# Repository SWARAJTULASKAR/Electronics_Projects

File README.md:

# Electronics_Projects
This repository showcases a collection of custom PCB design projects created using KiCad, Autodesk Fusion 360, and Autodesk EAGLE. Each project includes complete design files, simulations, 3D models, and fabrication-ready outputs.

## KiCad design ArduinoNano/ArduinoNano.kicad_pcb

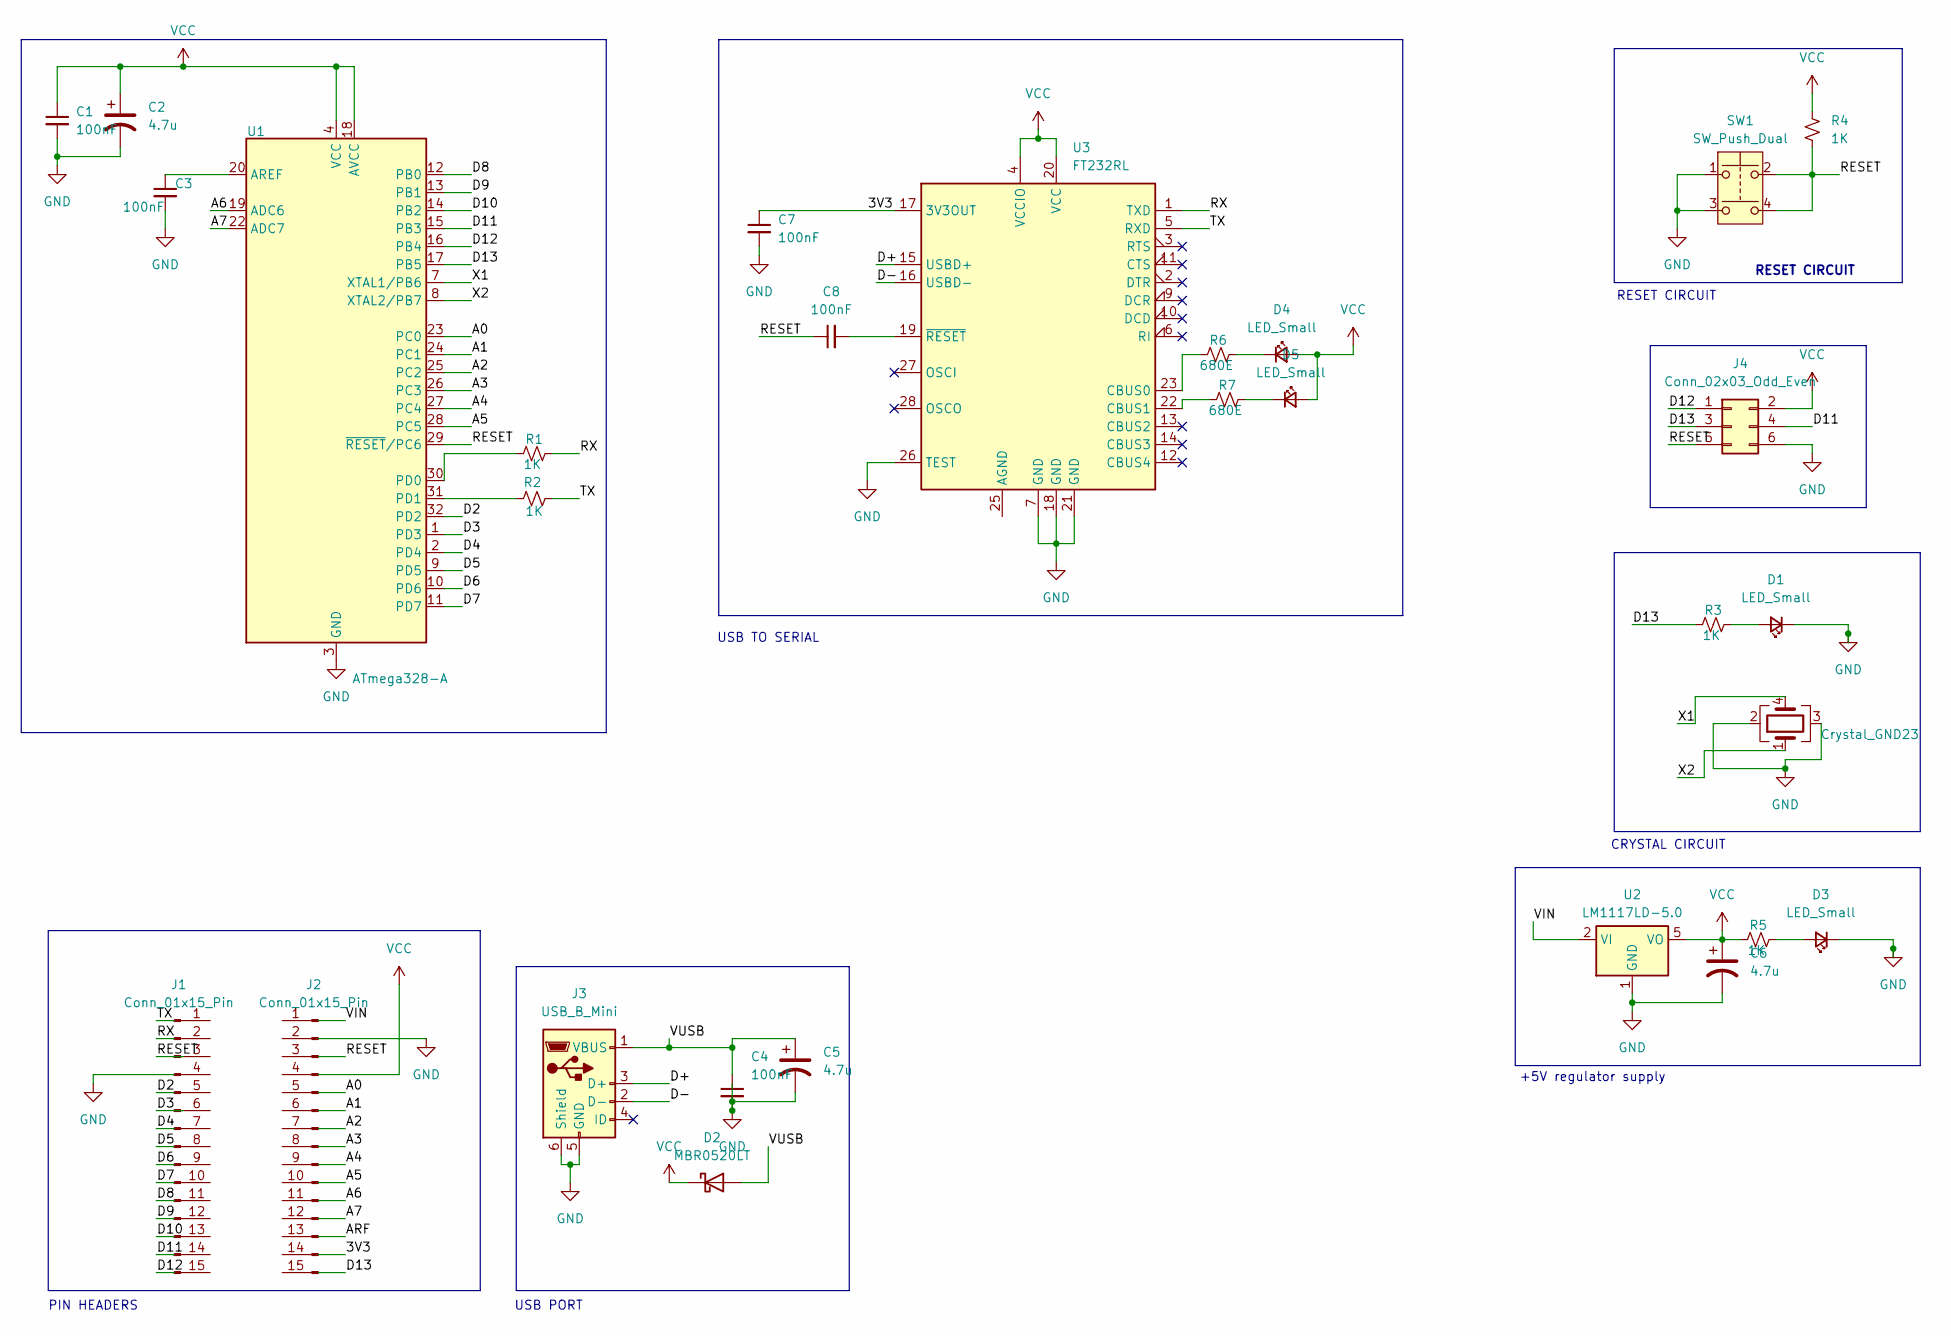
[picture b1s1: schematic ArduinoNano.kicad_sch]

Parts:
C1, C3, C4, C7, C8: 100nF; C_0603_1608Metric
C2, C5, C6: 4.7u; CP_EIA-1608-08_AVX-J
D1, D3, D4, D5: LED_Small; LED_1206_3216Metric
D2: MBR0520LT; D_SOD-123
J1, J2: Conn_01x15_Pin; Samtec_HPM-15-01-x-S_Straight_1x15_Pitch5.08mm
J3: USB_B_Mini; USB_Mini-B_Lumberg_2486_01_Horizontal
J4: Conn_02x03_Odd_Even; PinHeader_2x03_P2.54mm_Vertical
R1, R2, R3, R4, R5: 1K; R_01005_0402Metric
R6, R7: 680E; R_0402_1005Metric
SW1: SW_Push_Dual; SW_MEC_5GSH9
U1: ATmega328-A; TQFP-32_7x7mm_P0.8mm
U2: LM1117LD-5.0; WSON-8-1EP_4x4mm_P0.8mm_EP2.2x3mm
U3: FT232RL; SSOP-28_5.3x10.2mm_P0.65mm
Y1: Crystal_GND23; Crystal_SMD_Abracon_ABM3B-4Pin_5.0x3.2mm

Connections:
/3V3: C7.1, U3.17 (3V3OUT)
/A0: U1.23 (PC0)
/A1: U1.24 (PC1)
/A2: U1.25 (PC2)
/A3: U1.26 (PC3)
/A4: U1.27 (PC4)
/A5: U1.28 (PC5)
/A6: U1.19 (ADC6)
/A7: U1.22 (ADC7)
/D2: U1.32 (PD2)
/D3: U1.1 (PD3)
/D4: U1.2 (PD4)
/D5: U1.9 (PD5)
/D6: U1.10 (PD6)
/D7: U1.11 (PD7)
/D8: U1.12 (PB0)
/D9: U1.13 (PB1)
/D10: U1.14 (PB2)
/D11: J4.4, U1.15 (PB3)
/D12: J4.1, U1.16 (PB4)
/D13: J4.3, R3.1, U1.17 (PB5)
/D+: J3.3 (D+), U3.15 (USBD+)
/D-: J3.2 (D-), U3.16 (USBD-)
/RESET: C8.1, J4.5, R4.2, SW1.2, SW1.4, U1.29 (~RESET/PC6)
/RX: R1.2, U3.1 (TXD)
/TX: R2.2, U3.5 (RXD)
/VIN: U2.2 (VI), U2.3 (VI), U2.4 (VI)
/VUSB: C4.1, C5.1, D2.2 (A), J3.1 (VBUS)
GND: C1.2, C2.2, C3.2, C4.2, C5.2, C6.2, C7.2, D1.1 (K), D3.1 (K), J3.5 (GND), J3.6 (Shield), J4.6, SW1.1, SW1.3, U1.3 (GND), U1.5 (GND), U1.21 (GND), U2.1 (GND), U3.7 (GND), U3.18 (GND), U3.21 (GND), U3.26 (TEST), Y1.2, Y1.3
unnamed: D1.2 (A), R3.2
unnamed: D3.2 (A), R5.2
unnamed: D4.1 (K), R6.2
unnamed: D5.1 (K), R7.2
unnamed: C3.1, U1.20 (AREF)
unnamed: R1.1, U1.30 (PD0)
unnamed: R2.1, U1.31 (PD1)
unnamed: R6.1, U3.23 (CBUS0)
unnamed: R7.1, U3.22 (CBUS1)
unnamed: C8.2, U3.19 (~RESET)
VCC: C1.1, C2.1, C6.1, D2.1 (K), D4.2 (A), D5.2 (A), J4.2, R4.1, R5.1, U1.4 (VCC), U1.6 (VCC), U1.18 (AVCC), U2.5 (VO), U2.6 (VO), U2.7 (VO), U2.9 (VO), U3.4 (VCCIO), U3.20 (VCC)

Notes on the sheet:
CRYSTAL CIRCUIT
USB TO SERIAL
+5V regulator supply
PIN HEADERS
RESET CIRCUIT
RESET CIRCUIT
USB PORT

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
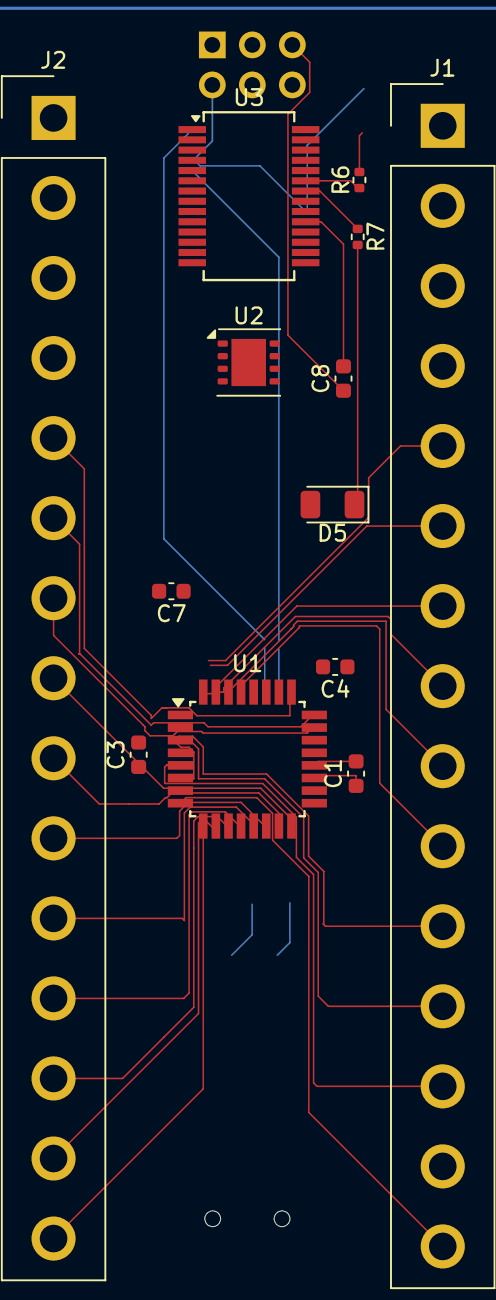
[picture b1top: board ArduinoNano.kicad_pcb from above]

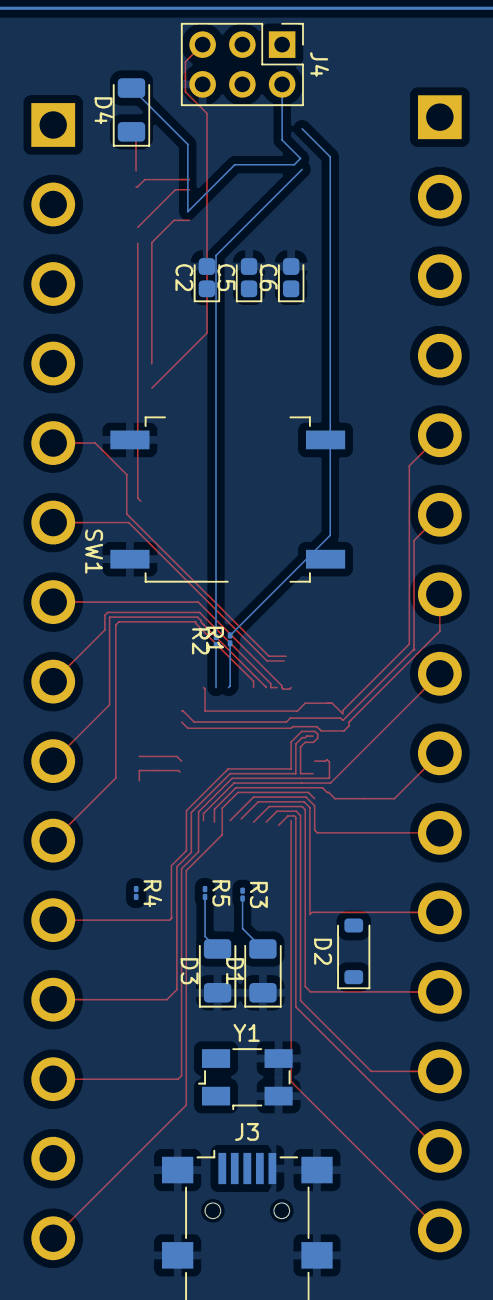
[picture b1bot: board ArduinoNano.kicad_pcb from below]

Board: 2 copper layers, 29 parts (16 on the bottom side), 25 nets.

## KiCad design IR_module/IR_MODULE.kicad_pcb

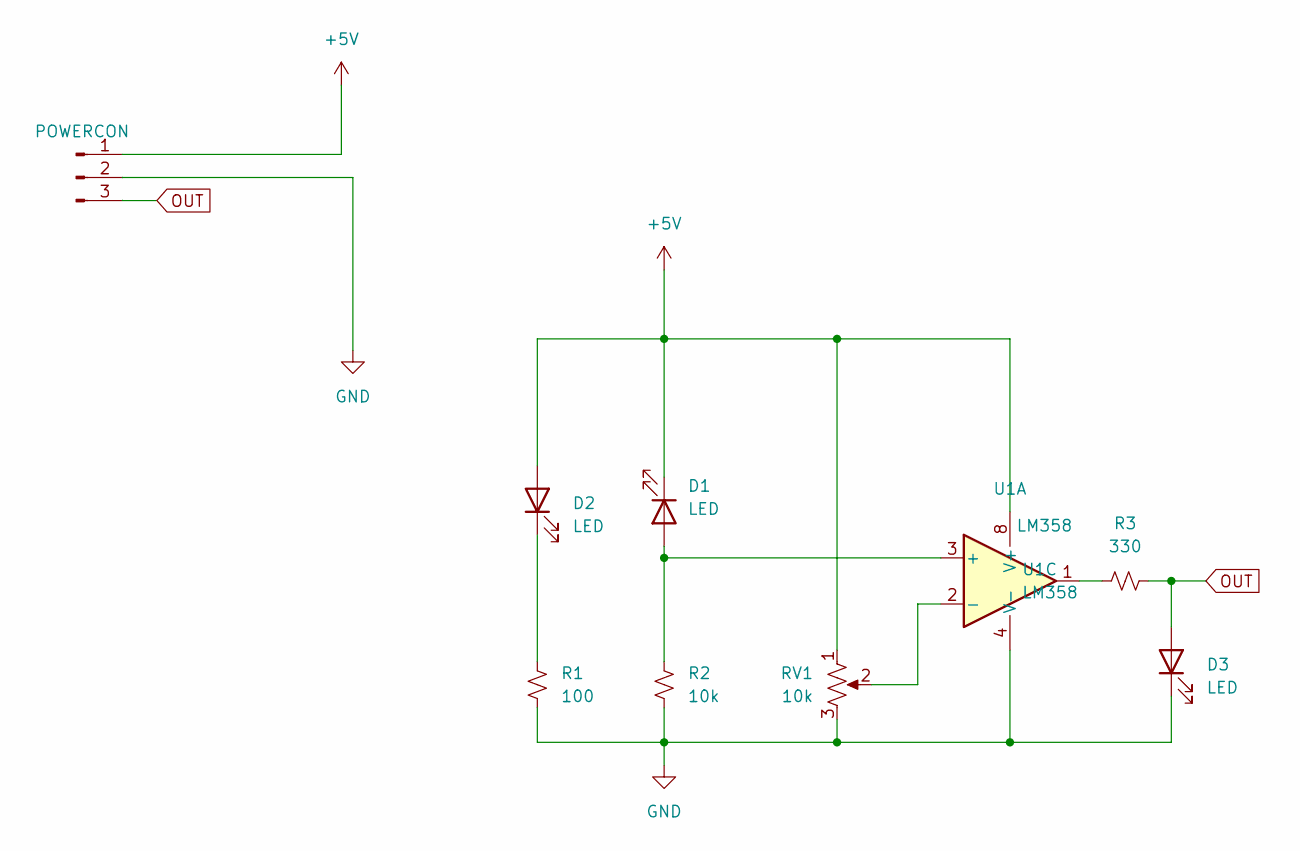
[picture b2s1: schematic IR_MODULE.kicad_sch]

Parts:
D1, D2: LED; LED_D3.0mm_Horizontal_O3.81mm_Z2.0mm
D3: LED; LED_1206_3216Metric
J1: POWERCON; PinHeader_1x03_P2.54mm_Horizontal
R1: 100; R_1206_3216Metric
R2: 10k; R_1206_3216Metric
R3: 330; R_1206_3216Metric
RV1: 10k; Potentiometer_Bourns_3266Y_Vertical
U1: LM358; DIP-8_W7.62mm_SMDSocket_SmallPads

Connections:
+5V: D1.1 (K), D2.2 (A), J1.1, RV1.1, U1.8 (V+)
GND: D3.1 (K), J1.2, R1.2, R2.2, RV1.3, U1.4 (V-)
unnamed: D1.2 (A), R2.1, U1.3 (+)
unnamed: D2.1 (K), R1.1
unnamed: R3.2, U1.1
unnamed: RV1.2, U1.2 (-)
OUT: D3.2 (A), J1.3, R3.1

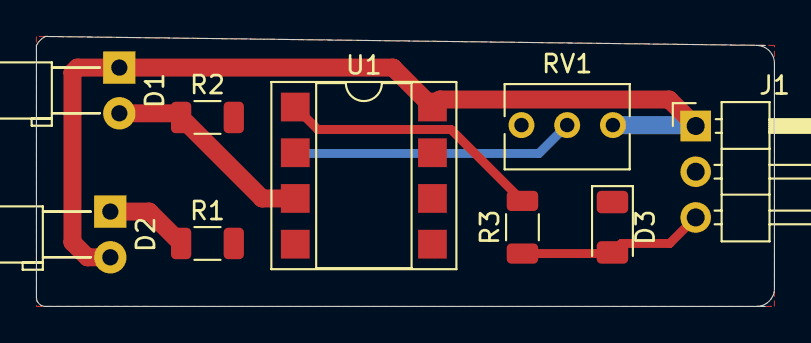
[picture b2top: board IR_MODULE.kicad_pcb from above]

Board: 2 copper layers, 41.0 x 15.0 mm, 9 parts (0 on the bottom side), 7 nets.

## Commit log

2025-05-08 Create IR1
2025-05-08 New File
2025-05-08 Create Arduino Nano Clone
2025-05-08 Create A1
2025-05-08 Add files via upload
    All data is upload but 3D PCB design is incomplete
2025-05-08 Create L1
2025-05-08 Add files via upload
    Data is uploaded
